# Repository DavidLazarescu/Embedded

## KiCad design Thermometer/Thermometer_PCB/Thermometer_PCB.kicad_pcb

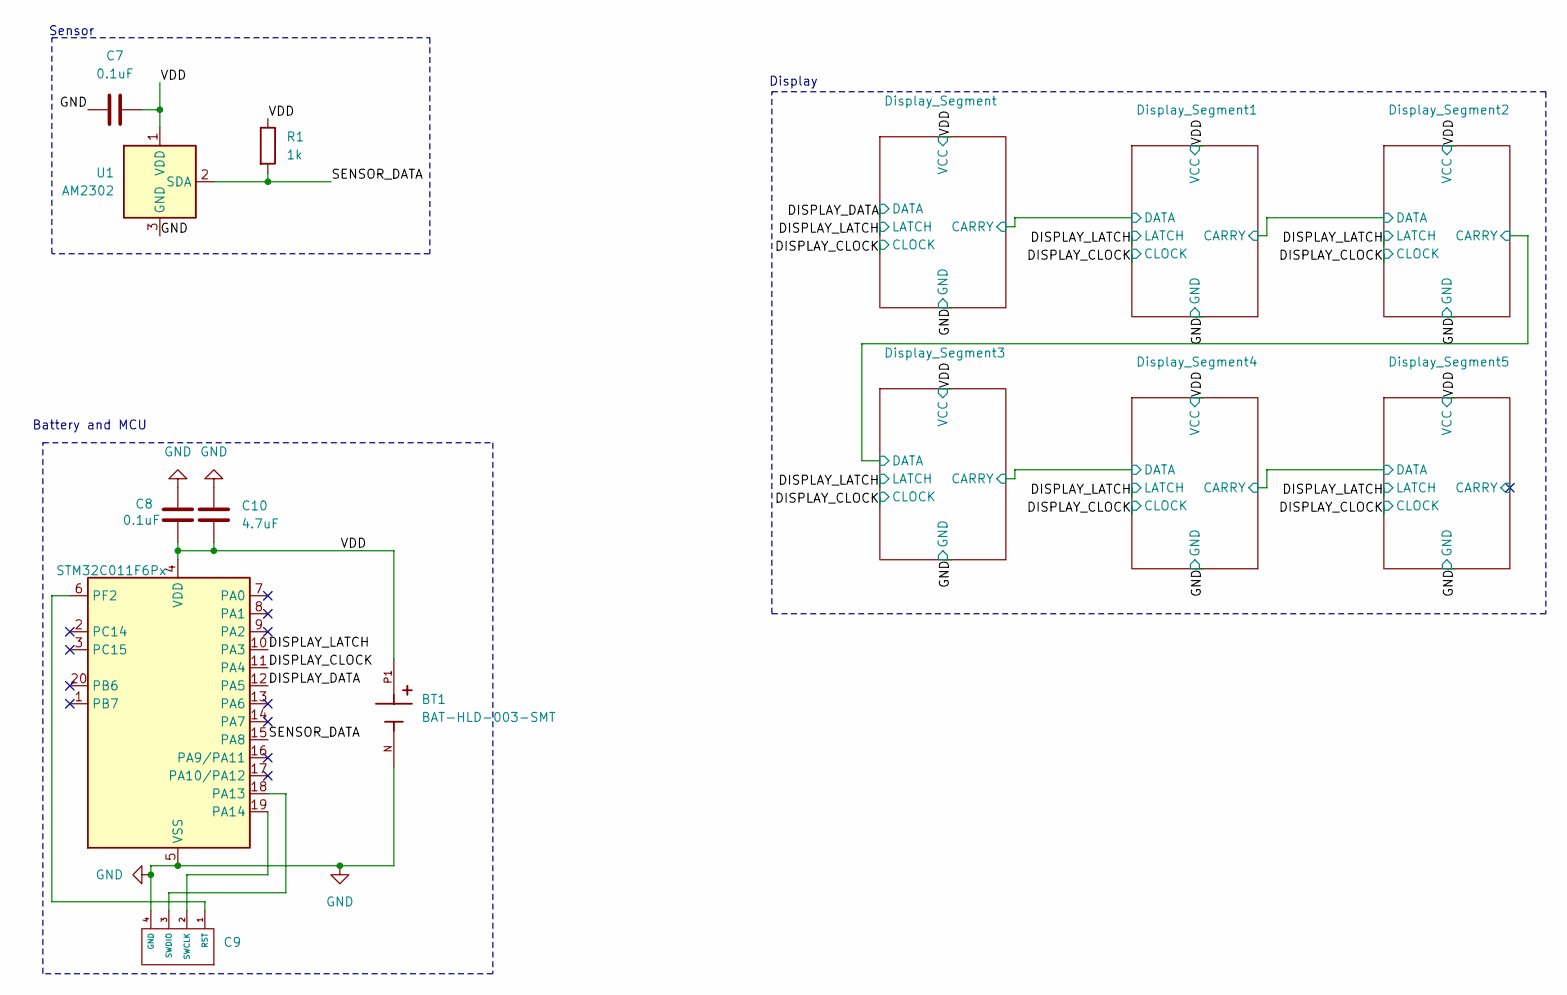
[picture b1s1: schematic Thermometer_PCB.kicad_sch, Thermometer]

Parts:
BT1: BAT-HLD-003-SMT
C7, C8: 0.1uF; Capacitor-0.1uF-0603-C125205
C9: SWD-Interface
C10: 4.7uF; Capacitor-4.7uF-0603-C76615
R1: 1k; Resistor-1kO-0603-C4410
U1: AM2302; ASAIR_AM2302_P2.54mm_Vertical
U9: STM32C011F6Px; TSSOP-20_4.4x6.5mm_P0.65mm

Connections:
/DISPLAY_CLOCK: U9.11 (PA4); also elsewhere on the board
/DISPLAY_DATA: U9.12 (PA5); also elsewhere on the board
/DISPLAY_LATCH: U9.10 (PA3); also elsewhere on the board
/SENSOR_DATA: R1.2, U1.2 (SDA), U9.15 (PA8)
/VDD: BT1.P1, C7.2, C8.2, C10.2, R1.1, U1.1 (VDD), U9.4 (VDD); also elsewhere on the board
GND: BT1.N, C7.1, C8.1, C9.4 (GND), C10.1, U1.3 (GND), U1.4 (GND), U9.5 (VSS); also elsewhere on the board
unnamed: C9.1 (RST), U9.6 (PF2)
unnamed: C9.2 (SWCLK), U9.19 (PA14)
unnamed: C9.3 (SWDIO), U9.18 (PA13)

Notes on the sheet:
Sensor
Display
Battery and MCU

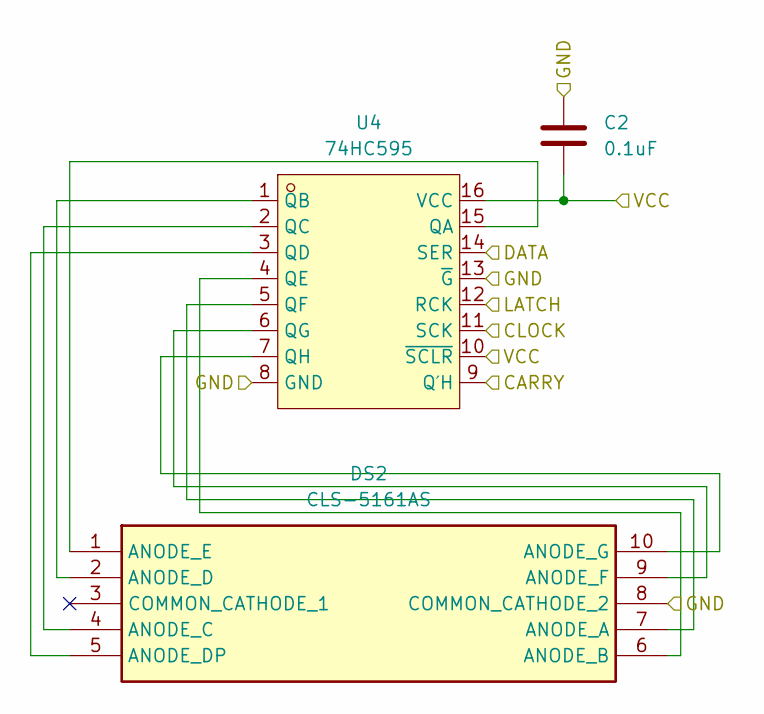
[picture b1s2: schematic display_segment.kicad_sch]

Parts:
C2: 0.1uF; Capacitor-0.1uF-0603-C125205
DS2: CLS-5161AS; DIPS1524W51P254L1260H800Q10N; Manufacturer_Part_Number CLS-5161AS
U4: 74HC595; SOP-16_L9.9-W3.9-P1.27-LS6.0-BL; LCSC Part C18164493

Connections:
/DISPLAY_CLOCK: U4.11 (SCK); also elsewhere on the board
/DISPLAY_LATCH: U4.12 (RCK); also elsewhere on the board
/Display_Segment1/CARRY: U4.9 (Q′H); also elsewhere on the board
/Display_Segment/CARRY: U4.14 (SER); also elsewhere on the board
/VDD: C2.2, U4.10 (~SCLR), U4.16 (VCC); also elsewhere on the board
GND: C2.1, DS2.8 (COMMON_CATHODE_2), U4.8 (GND), U4.13 (~G); also elsewhere on the board
unnamed: DS2.7 (ANODE_A), U4.5 (QF)
unnamed: DS2.6 (ANODE_B), U4.4 (QE)
unnamed: DS2.4 (ANODE_C), U4.2 (QC)
unnamed: DS2.2 (ANODE_D), U4.1 (QB)
unnamed: DS2.5 (ANODE_DP), U4.3 (QD)
unnamed: DS2.1 (ANODE_E), U4.15 (QA)
unnamed: DS2.9 (ANODE_F), U4.6 (QG)
unnamed: DS2.10 (ANODE_G), U4.7 (QH)

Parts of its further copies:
C1, C3, C4, C5, C6: 0.1uF; Capacitor-0.1uF-0603-C125205
DS1, DS3, DS4, DS5, DS6: CLS-5161AS; DIPS1524W51P254L1260H800Q10N; Manufacturer_Part_Number CLS-5161AS
U3, U5, U6, U7, U8: 74HC595; SOP-16_L9.9-W3.9-P1.27-LS6.0-BL; LCSC Part C18164493

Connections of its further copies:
/DISPLAY_CLOCK: U3.11 (SCK), U5.11 (SCK), U6.11 (SCK), U7.11 (SCK), U8.11 (SCK); also elsewhere on the board
/DISPLAY_DATA: U3.14 (SER); also elsewhere on the board
/DISPLAY_LATCH: U3.12 (RCK), U5.12 (RCK), U6.12 (RCK), U7.12 (RCK), U8.12 (RCK); also elsewhere on the board
/Display_Segment1/CARRY: U5.14 (SER); also elsewhere on the board
/Display_Segment2/CARRY: U5.9 (Q′H), U6.14 (SER)
/Display_Segment3/CARRY: U6.9 (Q′H), U7.14 (SER)
/Display_Segment4/CARRY: U7.9 (Q′H), U8.14 (SER)
/Display_Segment5/CARRY: U8.9 (Q′H)
/Display_Segment/CARRY: U3.9 (Q′H); also elsewhere on the board
/VDD: C1.2, C3.2, C4.2, C5.2, C6.2, U3.10 (~SCLR), U3.16 (VCC), U5.10 (~SCLR), U5.16 (VCC), U6.10 (~SCLR), U6.16 (VCC), U7.10 (~SCLR), U7.16 (VCC), U8.10 (~SCLR), U8.16 (VCC); also elsewhere on the board
GND: C1.1, C3.1, C4.1, C5.1, C6.1, DS1.8 (COMMON_CATHODE_2), DS3.8 (COMMON_CATHODE_2), DS4.8 (COMMON_CATHODE_2), DS5.8 (COMMON_CATHODE_2), DS6.8 (COMMON_CATHODE_2), U3.8 (GND), U3.13 (~G), U5.8 (GND), U5.13 (~G), U6.8 (GND), U6.13 (~G), U7.8 (GND), U7.13 (~G), U8.8 (GND), U8.13 (~G); also elsewhere on the board
unnamed: DS1.7 (ANODE_A), U3.5 (QF)
unnamed: DS1.6 (ANODE_B), U3.4 (QE)
unnamed: DS1.4 (ANODE_C), U3.2 (QC)
unnamed: DS1.2 (ANODE_D), U3.1 (QB)
unnamed: DS1.5 (ANODE_DP), U3.3 (QD)
unnamed: DS1.1 (ANODE_E), U3.15 (QA)
unnamed: DS1.9 (ANODE_F), U3.6 (QG)
unnamed: DS1.10 (ANODE_G), U3.7 (QH)
unnamed: DS3.7 (ANODE_A), U5.5 (QF)
unnamed: DS3.6 (ANODE_B), U5.4 (QE)
unnamed: DS3.4 (ANODE_C), U5.2 (QC)
unnamed: DS3.2 (ANODE_D), U5.1 (QB)
unnamed: DS3.5 (ANODE_DP), U5.3 (QD)
unnamed: DS3.1 (ANODE_E), U5.15 (QA)
unnamed: DS3.9 (ANODE_F), U5.6 (QG)
unnamed: DS3.10 (ANODE_G), U5.7 (QH)
unnamed: DS4.7 (ANODE_A), U6.5 (QF)
unnamed: DS4.6 (ANODE_B), U6.4 (QE)
unnamed: DS4.4 (ANODE_C), U6.2 (QC)
unnamed: DS4.2 (ANODE_D), U6.1 (QB)
unnamed: DS4.5 (ANODE_DP), U6.3 (QD)
unnamed: DS4.1 (ANODE_E), U6.15 (QA)
unnamed: DS4.9 (ANODE_F), U6.6 (QG)
unnamed: DS4.10 (ANODE_G), U6.7 (QH)
unnamed: DS5.7 (ANODE_A), U7.5 (QF)
unnamed: DS5.6 (ANODE_B), U7.4 (QE)
unnamed: DS5.4 (ANODE_C), U7.2 (QC)
unnamed: DS5.2 (ANODE_D), U7.1 (QB)
unnamed: DS5.5 (ANODE_DP), U7.3 (QD)
unnamed: DS5.1 (ANODE_E), U7.15 (QA)
unnamed: DS5.9 (ANODE_F), U7.6 (QG)
unnamed: DS5.10 (ANODE_G), U7.7 (QH)
unnamed: DS6.7 (ANODE_A), U8.5 (QF)
unnamed: DS6.6 (ANODE_B), U8.4 (QE)
unnamed: DS6.4 (ANODE_C), U8.2 (QC)
unnamed: DS6.2 (ANODE_D), U8.1 (QB)
unnamed: DS6.5 (ANODE_DP), U8.3 (QD)
unnamed: DS6.1 (ANODE_E), U8.15 (QA)
unnamed: DS6.9 (ANODE_F), U8.6 (QG)
unnamed: DS6.10 (ANODE_G), U8.7 (QH)

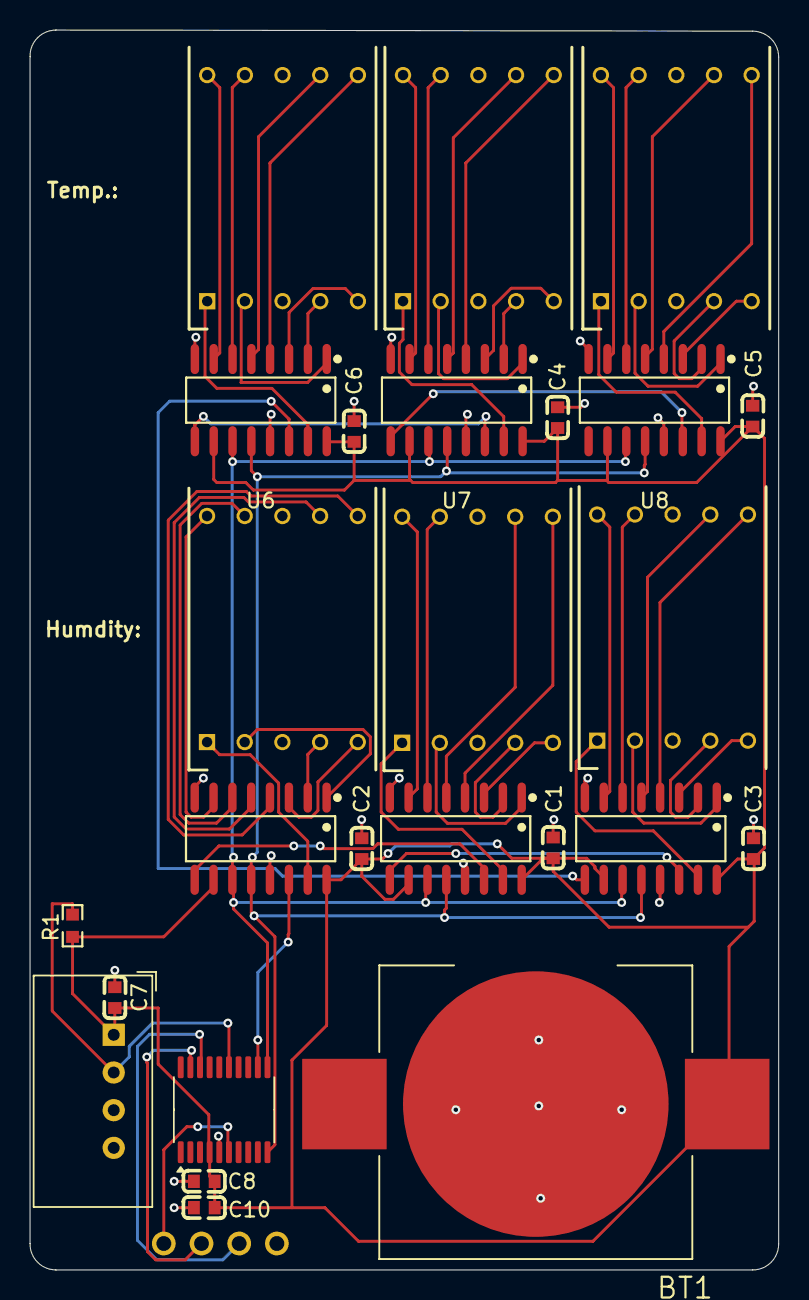
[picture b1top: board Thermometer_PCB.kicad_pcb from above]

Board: 2 copper layers, 50.5 x 83.6 mm, 26 parts (0 on the bottom side), 62 nets.

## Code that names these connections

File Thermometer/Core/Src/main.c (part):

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#define LOW_PERIOD 27
#define HIGH_PERIOD 70

#define DISPLAY_DATA_PIN GPIO_PIN_5
#define DISPLAY_LATCH_PIN GPIO_PIN_3
#define DISPLAY_CLOCK_PIN GPIO_PIN_4

#define SENSOR_DATA_PIN GPIO_PIN_6

int digits[10][8] = {
	{1, 1, 1, 0, 1, 1, 1, 0}, // 0
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  /*Configure GPIO pin Output Level */
  HAL_GPIO_WritePin(LD3_GPIO_Port, LD3_Pin, GPIO_PIN_RESET);

  /*Configure GPIO pins : PA3 PA4 PA5 */
  GPIO_InitStruct.Pin = GPIO_PIN_3|GPIO_PIN_4|GPIO_PIN_5;
  GPIO_InitStruct.Mode = GPIO_MODE_OUTPUT_PP;
  GPIO_InitStruct.Pull = GPIO_NOPULL;
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{
	for(int i = 0; i <= 9; ++i)
	{
		HAL_GPIO_WritePin(GPIOA, DISPLAY_LATCH_PIN, RESET);
		for(int k = 7; k >= 0; --k)
		{
			HAL_GPIO_WritePin(GPIOA, DISPLAY_CLOCK_PIN, RESET);
			delayUs(20);
			HAL_GPIO_WritePin(GPIOA, DISPLAY_DATA_PIN, digits[i][k]);
			delayUs(20);
			HAL_GPIO_WritePin(GPIOA, DISPLAY_CLOCK_PIN, SET);
		}
		HAL_GPIO_WritePin(GPIOA, DISPLAY_LATCH_PIN, SET);
		HAL_Delay(800);
	}
}
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
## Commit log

2024-10-21 Added thermometer project
2024-10-21 Measurement succeeded
2024-10-21 Added signal interpretation and console output
2024-10-22 Refactored
2024-10-22 Changed to repeat the reading; Refactored
2024-10-22 Added sleep mode after sampling data
2024-10-22 Decreased clock speed to 40MHz
2024-10-22 Improved string formatting
2024-11-05 Added PCB
2024-11-29 Remade PCB ; Changed File structure
2024-11-29 Added mounting holes
2024-12-02 Changed to hierarchical design, added capacitors and high amp connection pads
2024-12-06 Adjustments
2025-02-06 Finished software and improved PCB

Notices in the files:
Thermometer/Core/Src/main.c:
Copyright (c) 2024 STMicroelectronics.
All rights reserved.
This software is licensed under terms that can be found in the LICENSE file
